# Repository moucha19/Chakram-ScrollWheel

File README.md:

Chakram Scroll Wheel
===================

One day, scroll wheel on my Chakram X started misbehaving: sometimes scrolling in the wrong direction or not registering at all. After investigating, I concluded that the issue is most likely caused by a faulty encoder. Replacing it solved the problem, but I was no longer trusting the stock Kailh Red encoder, because the same issue was already reported online several times. To experiment with potentially higher-quality encoders without risking damage to the original part, I decided to recreate the entire scroll wheel PCB, staying as true to the original schematic and components as possible.

## Compatibility

| **Model**             | **Tested** | **Notes**                       |
| --------------------- | ---------- | ------------------------------- |
| Asus Chakram X        | ✅         | Fully functional                |
| Asus Chakram X Origin | ❓         | Untested, likely compatible     |
| Asus Chakram          | ❓         | Untested, compatibility unknown |
| Asus Chakram Core     | ❓         | Untested, compatibility unknown |

## Bill of materials

| Designator         | Footprint                     | Part link    |
|--------------------|-------------------------------|--------------|
| D1,D2,D3,D4,D6,D7  | SMD 0402 ESD protection       | [C1974929](https://www.lcsc.com/product-detail/C1974929.html )        |
| D5                 | *RGB LED daughterboard*       | [C2843813](https://www.lcsc.com/product-detail/C2843813.html)         |
| EN1                | Rotary encoder, 9mm height    | [688-EC10E1220501](https://mouser.com/ProductDetail/688-EC10E1220501) |
| J1                 | HRS(Hirose) FH12-8S-0.5SH(55) | [C597995](https://www.lcsc.com/product-detail/C597995.html)           |
| R1,R2              | 1k SMD 0402 Resistor          | [C11702](https://www.lcsc.com/product-detail/C11702.html)             |
| SW1                | EVQ-P0 series tactile switch  | [C395225](https://www.lcsc.com/product-detail/C395225.html)           |
 
Most of the parts listed are suggestions, and there are many compatible alternatives. This is particularly true for the encoder — selecting one depends on your personal preference, as different models vary in terms of tactility and scrolling force. I recommend starting with [this Reddit post](https://www.reddit.com/r/MouseReview/comments/18x4q6y/what_are_they_and_how_to_choose_mouse_encoders/) first, to see what's out there. 

However, regardless of the encoder you choose, **always use the 1k resistors** specified in the BOM. Do not use the resistor value mentioned in the encoder’s datasheet.

## Assembly

The board matches the original exactly, so simply connect the cable and screw it in.

#### Disclaimer

*This project is not affiliated with or endorsed by Asus. Use this design at your own risk. Ensure you follow proper safety protocols when handling electronic components and soldering.*

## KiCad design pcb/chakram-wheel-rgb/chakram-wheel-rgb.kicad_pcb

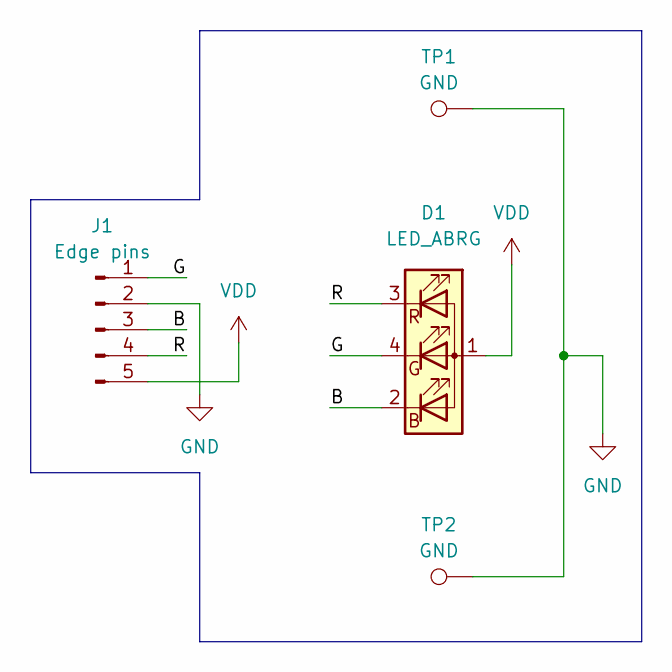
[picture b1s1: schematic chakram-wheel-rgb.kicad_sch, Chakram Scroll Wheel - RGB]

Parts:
D1: LED_ABRG; LED_RGB_Wuerth-PLCC4_3.2x2.8mm_150141M173100
J1: Edge pins; LED_Chakram_Edge
TP1, TP2: GND; TestPoint_THTPad_D2.0mm_Drill1.0mm

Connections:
/B: D1.2 (BK), J1.3
/G: D1.4 (GK), J1.1
/R: D1.3 (RK), J1.4
GND: J1.2, TP1.1, TP2.1
VDD: D1.1 (A), J1.5

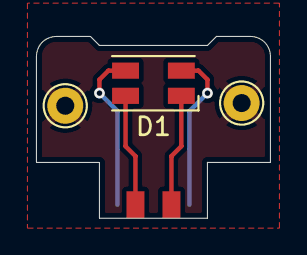
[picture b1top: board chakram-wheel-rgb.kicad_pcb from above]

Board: 2 copper layers, 13.0 x 10.1 mm, 4 parts (1 on the bottom side), 5 nets.

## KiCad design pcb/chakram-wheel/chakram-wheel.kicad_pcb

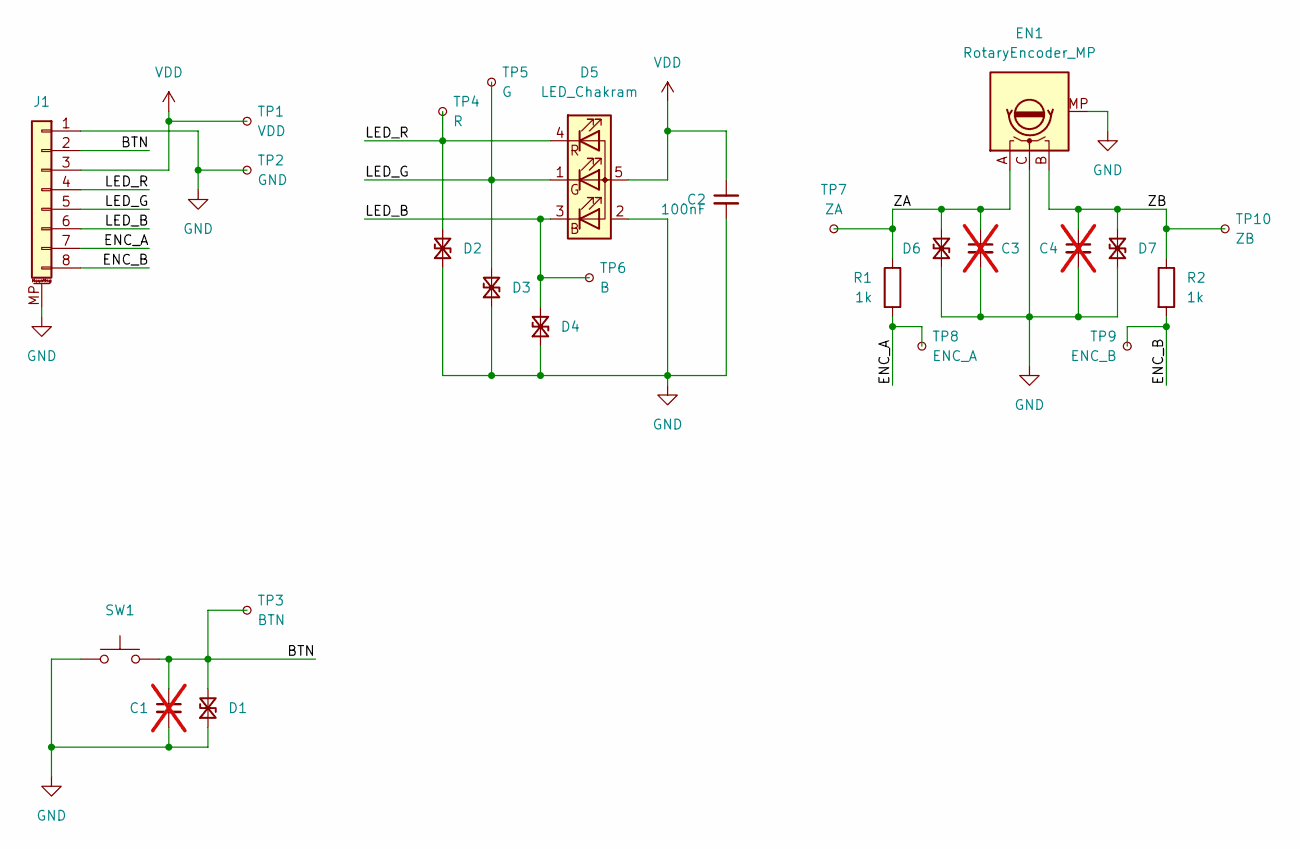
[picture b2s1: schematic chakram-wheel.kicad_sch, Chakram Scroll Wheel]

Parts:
C1, C3, C4: C_0402_1005Metric; not fitted
C2: 100nF; C_0402_1005Metric
D1, D2, D3, D4, D6, D7: D_TVS_Small; D_0402_1005Metric
D5: LED_Chakram
EN1: RotaryEncoder_MP; RotaryEncoder_Alps_EC10E
J1: FPC Connector; Hirose_FH12-8S-0.5SH_1x08-1MP_P0.50mm_Horizontal
R1, R2: 1k; R_0402_1005Metric
SW1: SW_Push_EVQP0
TP1: VDD; TestPoint_Pad_D1.0mm
TP2: GND; TestPoint_Pad_D1.0mm
TP3: BTN; TestPoint_Pad_D1.0mm
TP4: R; TestPoint_Pad_D1.0mm
TP5: G; TestPoint_Pad_D1.0mm
TP6: B; TestPoint_Pad_D1.0mm
TP7: ZA; TestPoint_Pad_D1.0mm
TP8: ENC_A; TestPoint_Pad_D1.0mm
TP9: ENC_B; TestPoint_Pad_D1.0mm
TP10: ZB; TestPoint_Pad_D1.0mm

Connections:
/BTN: C1.1, D1.2 (A2), J1.2, SW1.2, TP3.1
/ENC_A: J1.7, R1.2, TP8.1
/ENC_B: J1.8, R2.2, TP9.1
/LED_B: D4.2 (A2), D5.3 (BK), J1.6, TP6.1
/LED_G: D3.2 (A2), D5.1 (GK), J1.5, TP5.1
/LED_R: D2.2 (A2), D5.4 (RK), J1.4, TP4.1
/ZA: C3.1, D6.2 (A2), EN1.A, R1.1, TP7.1
/ZB: C4.1, D7.2 (A2), EN1.B, R2.1, TP10.1
GND: C1.2, C2.2, C3.2, C4.2, D1.1 (A1), D2.1 (A1), D3.1 (A1), D4.1 (A1), D5.2 (EP), D6.1 (A1), D7.1 (A1), EN1.C, EN1.MP, J1.1, J1.MP (MountPin), SW1.1, TP2.1
VDD: C2.1, D5.5 (A), J1.3, TP1.1

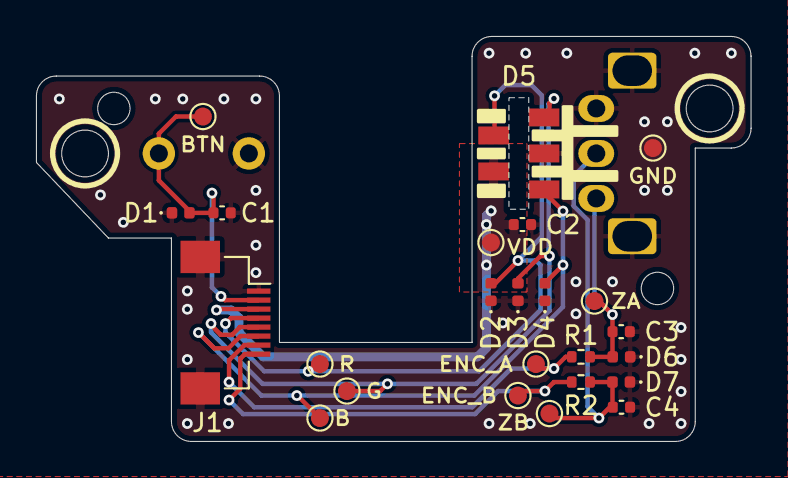
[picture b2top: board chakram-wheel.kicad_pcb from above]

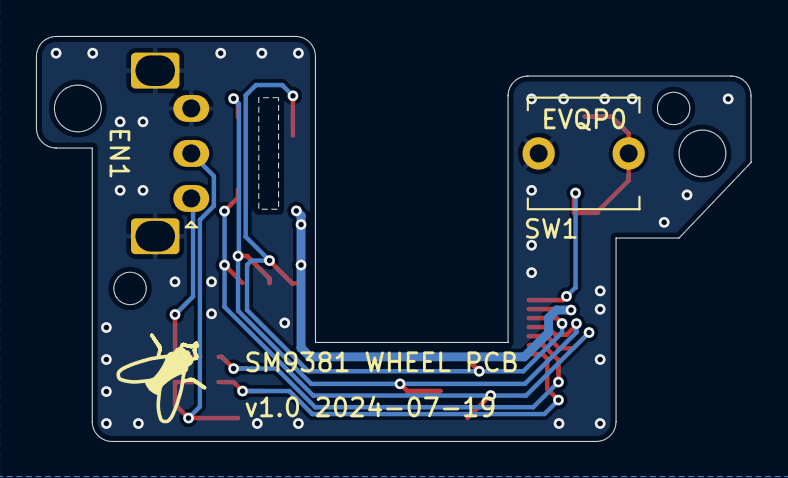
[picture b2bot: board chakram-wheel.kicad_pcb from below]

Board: 2 copper layers, 39.7 x 22.5 mm, 26 parts (2 on the bottom side), 10 nets.

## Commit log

2024-07-04 Updated hole and component positions
2024-07-04 Improved encoder symbol to also include MP pins and connected them to GND
2024-07-04 Added testpoints
2024-07-04 Positioned all test points
2024-07-04 Routed all signals
2024-07-04 Updated pad type for LED slot pads
2024-07-04 Added button part name to silkscreen
2024-07-04 Added more silkscreen elements, minor cleanups
2024-07-04 Added ground stitching
2024-07-04 Adjusted encoder MP pad position and size
2024-07-04 Rounded corners
2024-07-04 Fixed swapped ENC_A and ENC_B signals on J1
2024-07-18 Adjusted RGB slot dimensions, added RGB board
2024-07-19 Added generated schematics, updated silkscreen and RGB board shape
2024-07-19 Added fabrication output settings
2024-12-29 Added photos and description into README

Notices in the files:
pcb/chakram-wheel-rgb/chakram-wheel-rgb.kicad_pcb:
Licensed under CERN-OHL-W v2
